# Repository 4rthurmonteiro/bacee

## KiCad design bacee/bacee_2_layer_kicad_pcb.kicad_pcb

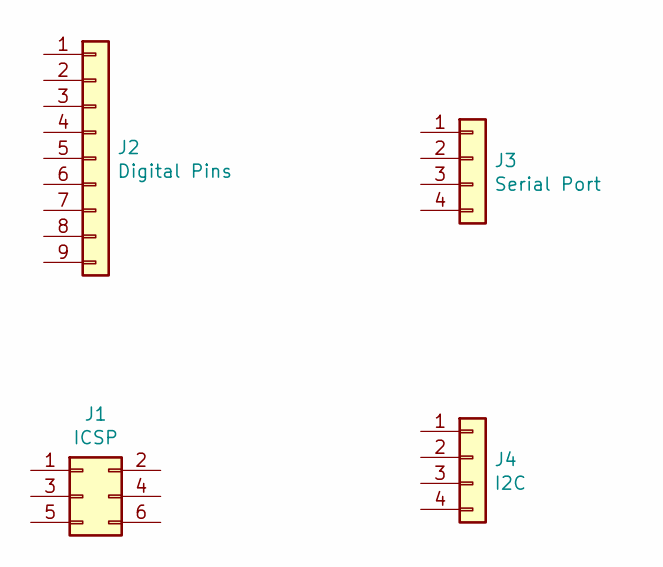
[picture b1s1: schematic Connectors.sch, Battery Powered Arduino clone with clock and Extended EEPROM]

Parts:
J1: ICSP; PinSocket_2x03_P2.54mm_Vertical
J2: Digital Pins; PinSocket_1x09_P2.54mm_Vertical
J3: Serial Port; PinSocket_1x04_P2.54mm_Vertical
J4: I2C; PinSocket_1x04_P2.54mm_Vertical

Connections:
/D2: J2.1; also elsewhere on the board
/D3: J2.2; also elsewhere on the board
/D4: J2.3; also elsewhere on the board
/D5: J2.4; also elsewhere on the board
/D6: J2.5; also elsewhere on the board
/D7: J2.6; also elsewhere on the board
/D8: J2.7; also elsewhere on the board
/MISO: J1.1; also elsewhere on the board
/MOSI: J1.4; also elsewhere on the board
/RESET: J1.5; also elsewhere on the board
/RX: J3.3; also elsewhere on the board
/SCK: J1.3, J4.4; also elsewhere on the board
/SDA: J4.3; also elsewhere on the board
/TX: J3.4; also elsewhere on the board
/VCC: J1.2, J2.9, J3.2, J4.2; also elsewhere on the board
GNDPWR: J1.6, J2.8, J3.1, J4.1; also elsewhere on the board

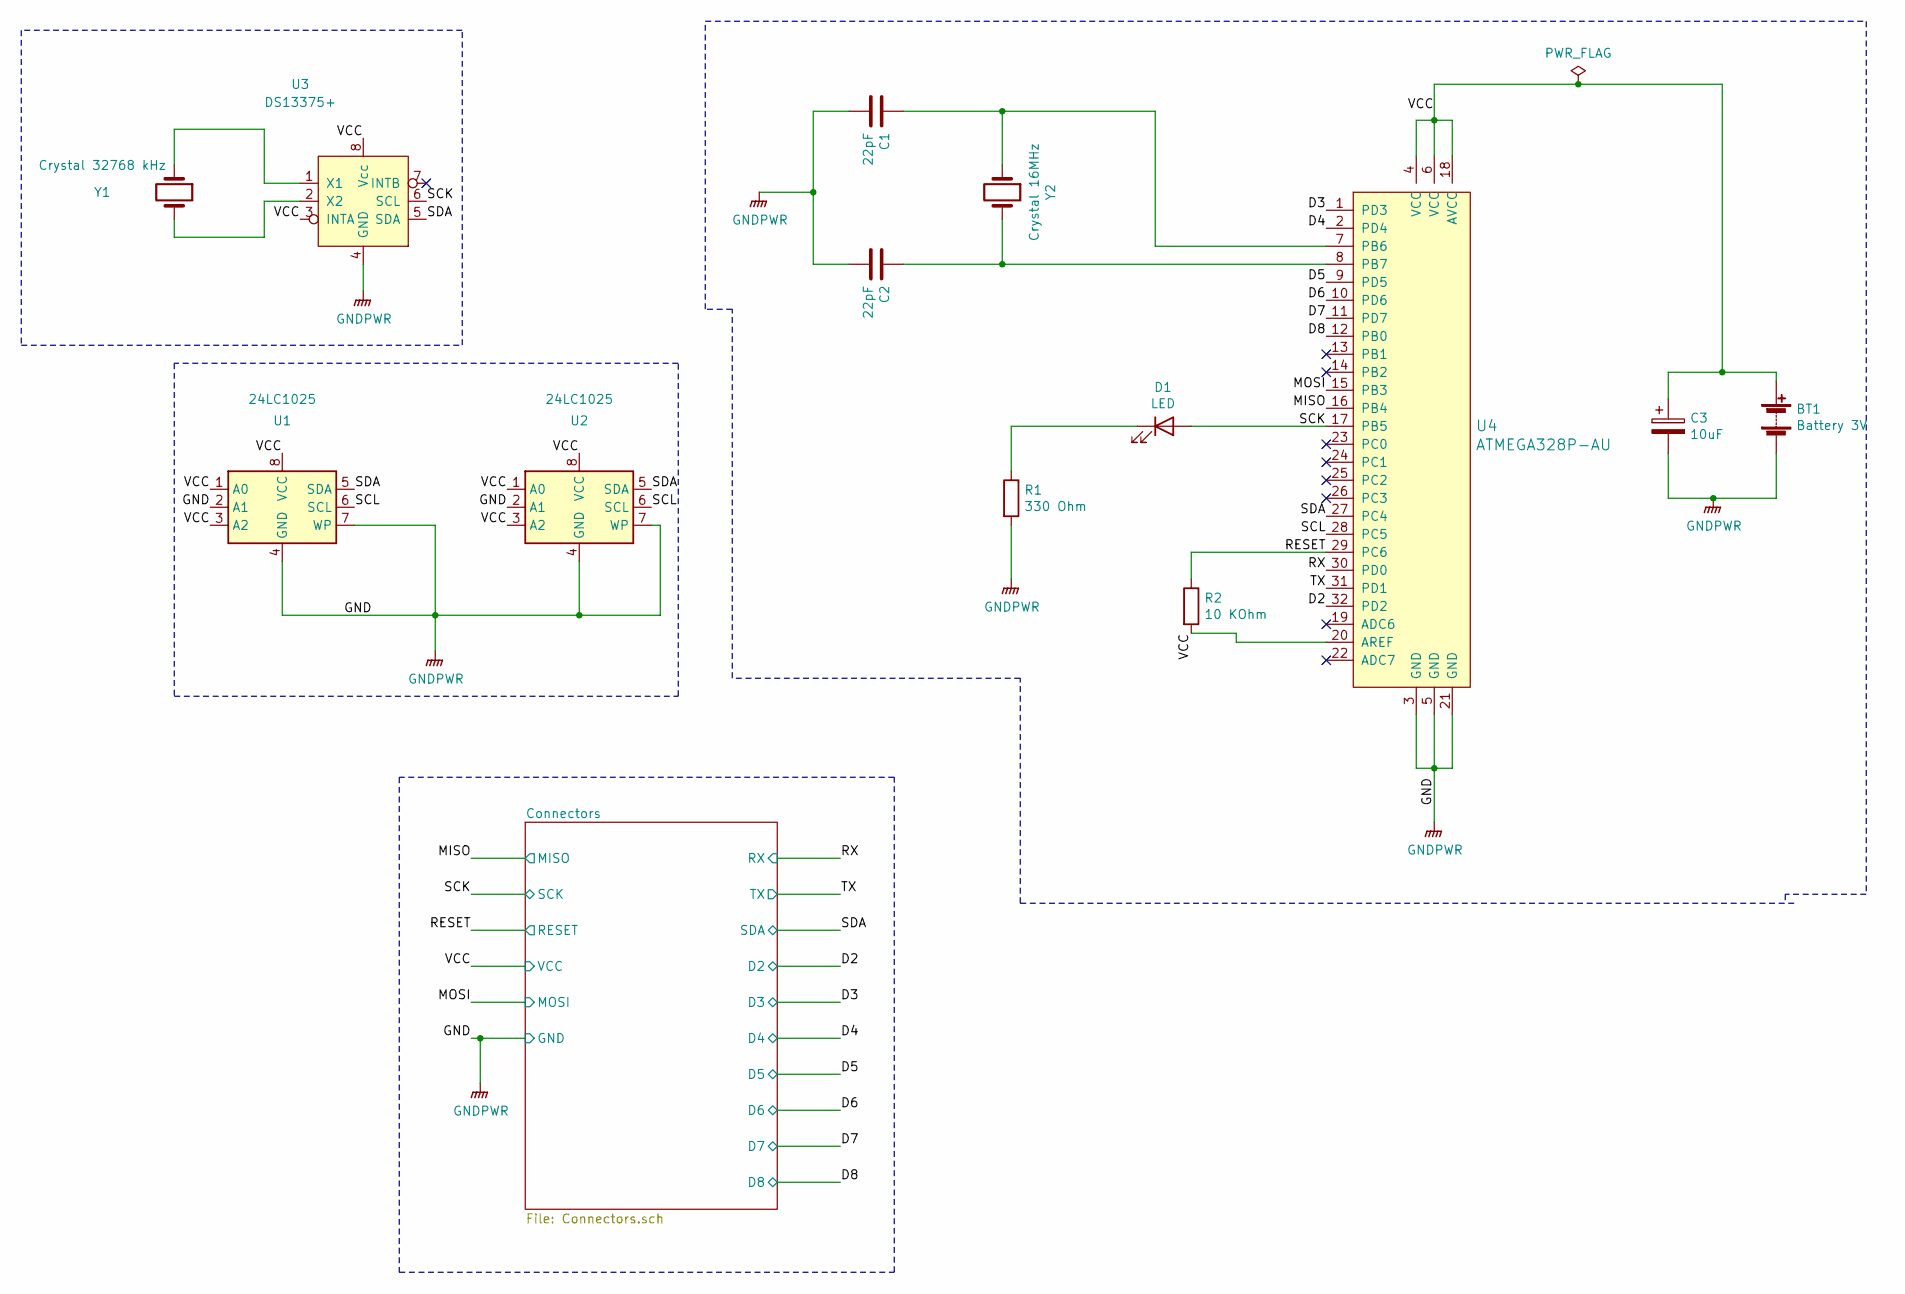
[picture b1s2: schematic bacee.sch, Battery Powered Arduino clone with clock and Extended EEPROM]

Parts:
BT1: Battery 3V; PinHeader_1x02_P2.54mm_Vertical
C1, C2: 22pF; C_0504_1310Metric_Pad0.83x1.28mm_HandSolder
C3: 10uF; C_0504_1310Metric_Pad0.83x1.28mm_HandSolder
D1: LED; LED_0805_2012Metric_Pad1.15x1.40mm_HandSolder
R1: 330 Ohm; R_0805_2012Metric_Pad1.20x1.40mm_HandSolder
R2: 10 KOhm; R_0805_2012Metric_Pad1.20x1.40mm_HandSolder
U1, U2: 24LC1025; SOIJ-8_5.3x5.3mm_P1.27mm
U3: DS13375+; SO-8_5.3x6.2mm_P1.27mm
U4: ATMEGA328P-AU; TQFP-32_7x7mm; MPN ATMEGA328P-AU; Digi-Key_PN ATMEGA328P-AU-ND
Y1: Crystal 32768 kHz; Crystal_SMD_MicroCrystal_CC7V-T1A-2Pin_3.2x1.5mm
Y2: Crystal 16MHz; Crystal_SMD_5032-2Pin_5.0x3.2mm_HandSoldering

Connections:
/D2: U4.32 (PD2); also elsewhere on the board
/D3: U4.1 (PD3); also elsewhere on the board
/D4: U4.2 (PD4); also elsewhere on the board
/D5: U4.9 (PD5); also elsewhere on the board
/D6: U4.10 (PD6); also elsewhere on the board
/D7: U4.11 (PD7); also elsewhere on the board
/D8: U4.12 (PB0); also elsewhere on the board
/MISO: U4.16 (PB4); also elsewhere on the board
/MOSI: U4.15 (PB3); also elsewhere on the board
/RESET: R2.1, U4.29 (PC6); also elsewhere on the board
/RX: U4.30 (PD0); also elsewhere on the board
/SCK: D1.2 (A), U3.6 (SCL), U4.17 (PB5); also elsewhere on the board
/SCL: U1.6 (SCL), U2.6 (SCL), U4.28 (PC5)
/SDA: U1.5 (SDA), U2.5 (SDA), U3.5 (SDA), U4.27 (PC4); also elsewhere on the board
/TX: U4.31 (PD1); also elsewhere on the board
/VCC: BT1.1 (+), C3.1, R2.2, U1.1 (A0), U1.3 (A2), U1.8 (VCC), U2.1 (A0), U2.3 (A2), U2.8 (VCC), U3.3 (INTA), U3.8 (Vcc), U4.4 (VCC), U4.6 (VCC), U4.18 (AVCC), U4.20 (AREF); also elsewhere on the board
GNDPWR: BT1.2 (-), C1.2, C2.2, C3.2, R1.2, U1.2 (A1), U1.4 (GND), U1.7 (WP), U2.2 (A1), U2.4 (GND), U2.7 (WP), U3.4 (GND), U4.3 (GND), U4.5 (GND), U4.21 (GND); also elsewhere on the board
unnamed: C1.1, U4.7 (PB6), Y2.1
unnamed: C2.1, U4.8 (PB7), Y2.2
unnamed: D1.1 (K), R1.1
unnamed: U3.1 (X1), Y1.1
unnamed: U3.2 (X2), Y1.2

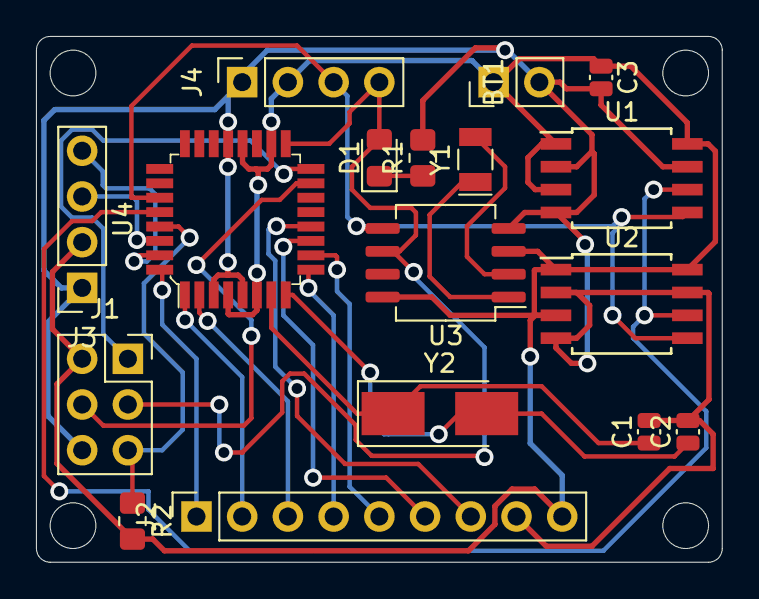
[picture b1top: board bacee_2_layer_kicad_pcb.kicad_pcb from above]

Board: 2 copper layers, 38.1 x 29.2 mm, 17 parts (0 on the bottom side), 22 nets.

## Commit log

2021-08-09 first
2021-08-11 wip: wiring
2021-08-15 done
